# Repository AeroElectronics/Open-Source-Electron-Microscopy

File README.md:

# Open Source Electron Microscopy

This is not the first or last attempt at making open source electron microscopy a reality. Many others have attempted this large and difficult task before with varying specialties and contributions. I have learned a great deal from other's work in this area and it is my hope that I can make a contribution too. It is through the collective effort and ability of the open source community that progress on such large and difficult tasks may be realized.

My work so far has focused on the control electronics which can be used to drive electron microscopes. This is an essential first step that can (mostly) preceed the design of the electron optics. I'm hoping that by lowering the barrier to entry, others can work on this exciting task.

**Note to readers! This repo is quite new, many of the currently uploaded works are my most recent iterations (old designs have not been uploaded) and have not yet been tested. Please check the **

I've worked on a few areas, see the links below:

[Backplane](./Backplane/README.md)

[Coil drivers](./DeflectionCoilDrivers/README.md)

[Resistor/Inductor Substitution board](./SubstitutionBoard/README.md)

[Raster generator](./RasterGenerator/README.md)

Remember, this project is still under development. Use at your own risk. This work is licenced under CERN OHL V2 S. Please see license file.

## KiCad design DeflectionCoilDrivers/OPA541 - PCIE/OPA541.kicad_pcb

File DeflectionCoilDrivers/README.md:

# Deflecion Coil Drivers
Deflection coil drivers are the electronics that push current into the magnetic lenses that raster the electron beam around the sample. A good deflection coil driver is high bandwidth, fast slewing, low noise, low distortion, low drift, and can operate over a large dynamic range. These constraints make practical design considerably more involved than I anticipated.

First, a few notes on deflection coil drivers generally. Since the magnetic field produced by a deflection coil is proportional to the current through it. This means that a deflection coil driver is essentially a 'transconductance amplifier' which converts a voltage signal input (from a DAC or something) that requests current, to a realized current on the coil.

Existing electron microscopes have used a variety of design approaches. I have designed several deflection coil drivers, shown below.

## Single ended coil driver
Single ended coil drivers are where you control the voltage on one side of your load, and ground the other side. This is simpler than a bridge topology and easier to work with generally, but it makes the sacrifice of giving up halving the maximum voltage difference you can apply to your load and limiting your slew rate as compared to two amplifiers. These designs are comparitively easy to work with and one require one power OpAmp and some supporting electronics. If you are ok with slow speeds, single ended is likely fine.

The picture below is my latest iteration of a somewhat but not entirely tested version. Will report back after testing this one.

## Bridge topology howland current pump
The bridge topology howland current pump is essentially two power OpAmps which act to source and sink current to and from the load. The load is positioned between the outputs of the two power OpAmps. With this topology the slew rate and maximum achivable voltage doubles as compared to a single ended design where one end of the load is grounded. I attempted this design using OPA548 amplifiers but was displeased with the speed. I have redesigned this board to accept other opamps and will revisit this in the future.

The picture below I have partially tested with some modifications. After some pain, I now think the OPA548 may be unsuitable for the task.

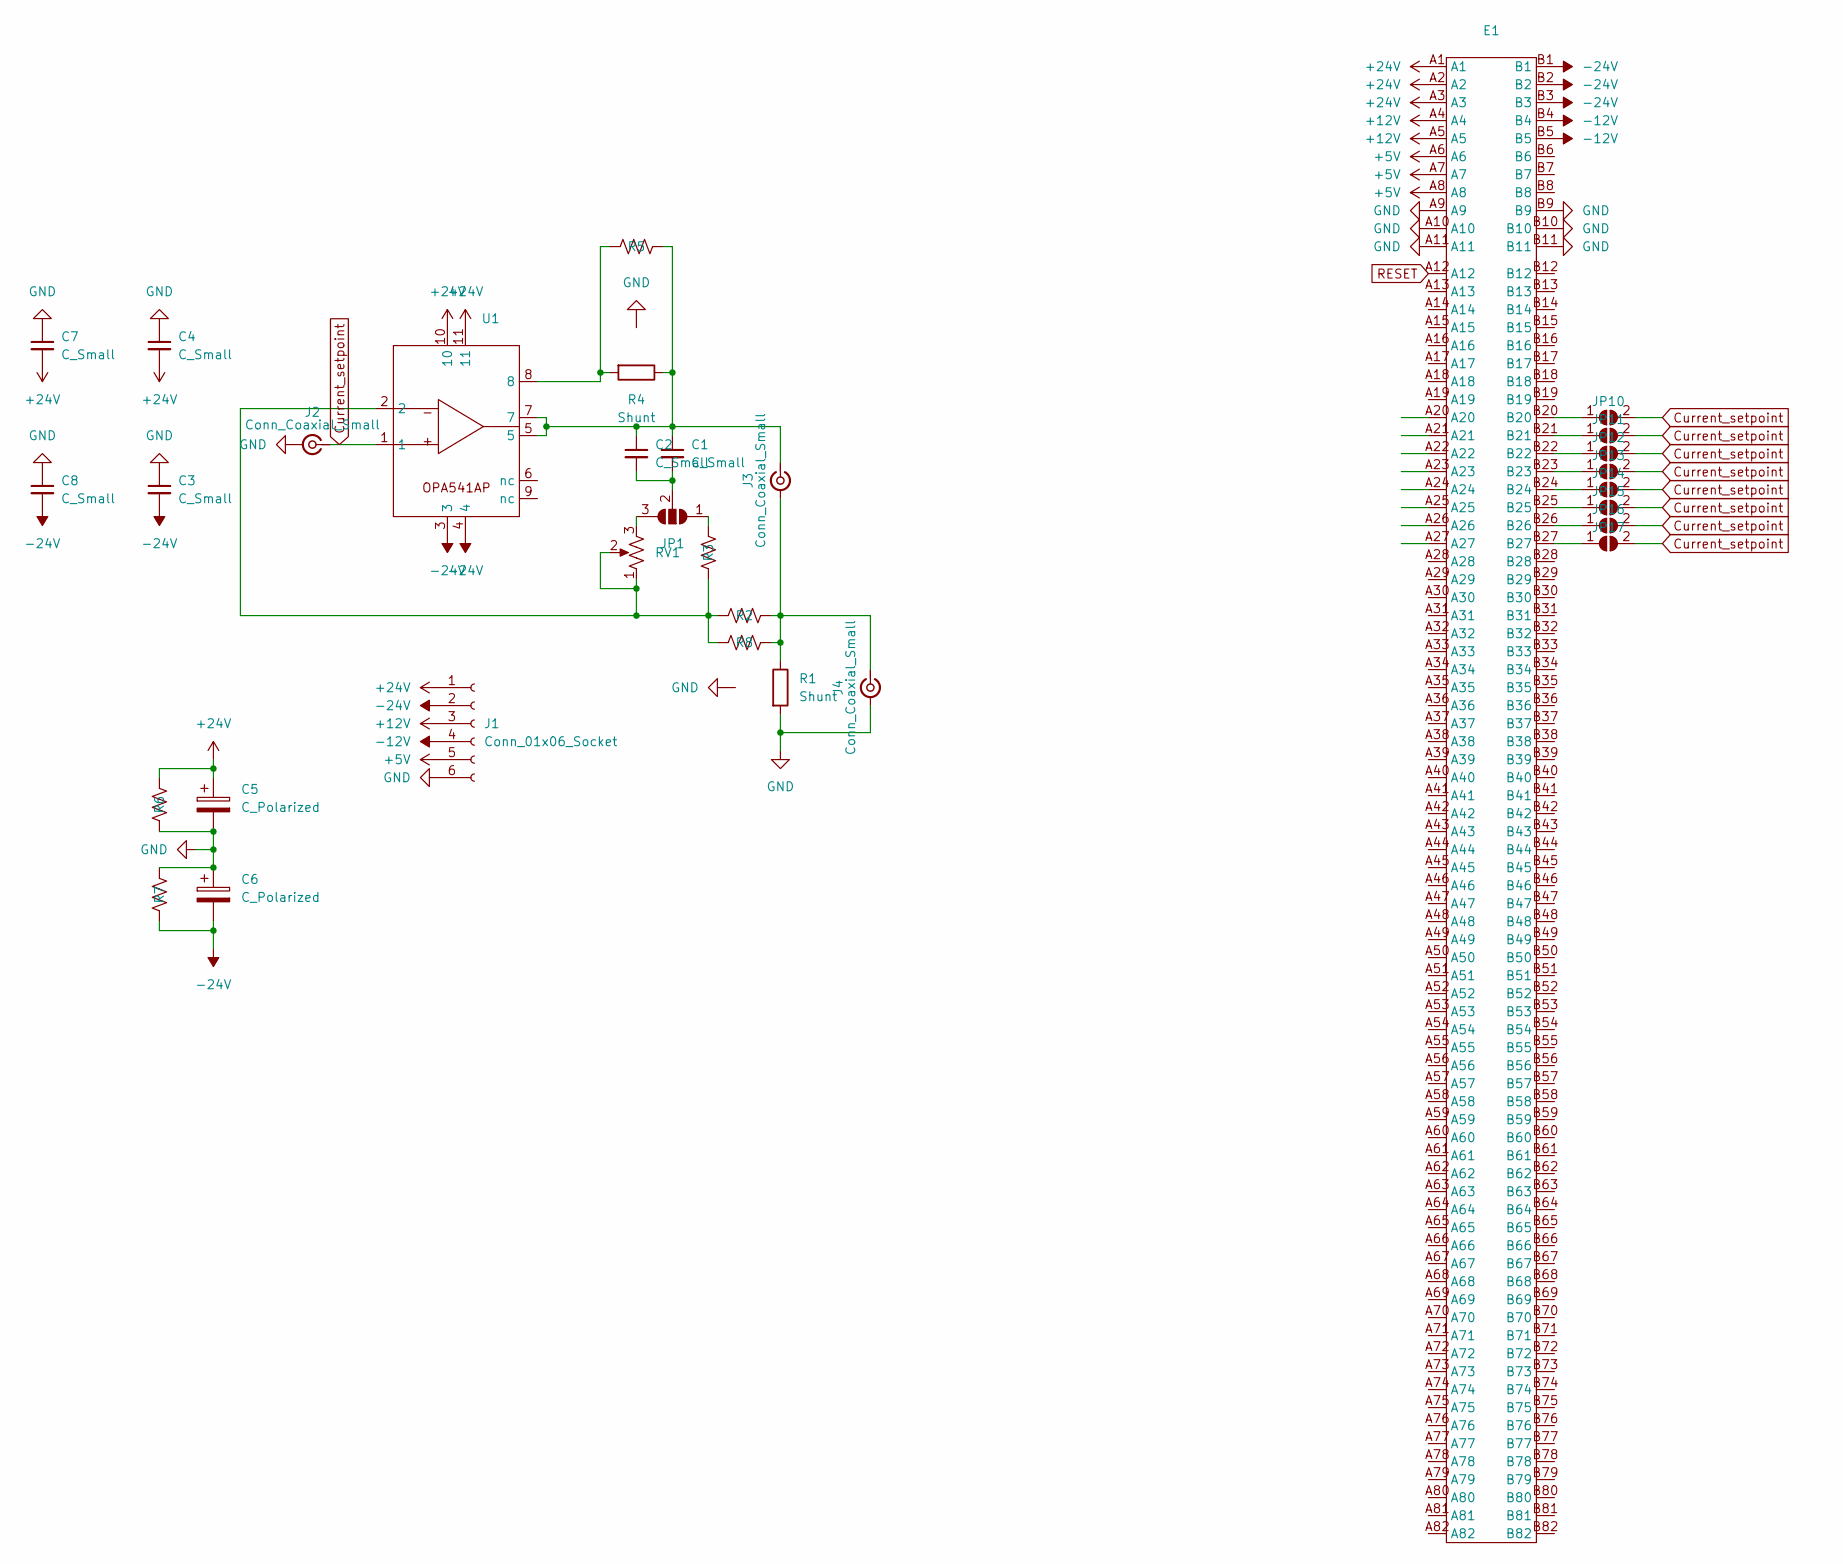
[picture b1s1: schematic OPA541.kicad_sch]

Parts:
C1, C3, C4, C7, C8: C_Small; C_0603_1608Metric_Pad1.08x0.95mm_HandSolder
C2: C_Small; C_Disc_D6.0mm_W2.5mm_P5.00mm
C5, C6: C_Polarized; CP_Radial_D10.0mm_P5.00mm
E1: BUS_PCIexpress_x16
J1: Conn_01x06_Socket; PhoenixContact_MC_1,5_6-GF-3.81_1x06_P3.81mm_Horizontal_Thr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
J2, J3, J4: Conn_Coaxial_Small; BNC_Amphenol_B6252HB-NPP3G-50_Horizontal
JP1: SolderJumper_3_Open; SolderJumper-3_P1.3mm_Open_RoundedPad1.0x1.5mm
JP10, JP11, JP12, JP13, JP14, JP15, JP16, JP17: SolderJumper_2_Open; SolderJumper-2_P1.3mm_Open_RoundedPad1.0x1.5mm
R1, R4: Shunt; TO-263-2_TabPin1
R2: 1k; C_0603_1608Metric_Pad1.08x0.95mm_HandSolder
R3: 20k; C_0603_1608Metric_Pad1.08x0.95mm_HandSolder
R5: 0.3; R_Axial_DIN0204_L3.6mm_D1.6mm_P7.62mm_Horizontal
R6, R7: 100k; R_0603_1608Metric_Pad0.98x0.95mm_HandSolder
R8: 1k; C_Disc_D6.0mm_W2.5mm_P5.00mm
RV1: R_Potentiometer_US; Potentiometer_Bourns_3269P_Horizontal
U1: TO-220-11_P3.4x5.08mm_StaggerOdd_Lead4.85mm_Vertical

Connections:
+5V: E1.A6, E1.A7, E1.A8, J1.5
+12V: E1.A4, E1.A5, J1.3
+24V: C4.2, C5.1, C7.2, E1.A1, E1.A2, E1.A3, J1.1, R6.2, U1.10, U1.11
-12V: E1.B4, E1.B5, J1.4
-24V: C3.2, C6.2, C8.2, E1.B1, E1.B2, E1.B3, J1.2, R7.1, U1.3, U1.4
Current_setpoint: J2.1 (In), JP10.2 (B), JP11.2 (B), JP12.2 (B), JP13.2 (B), JP14.2 (B), JP15.2 (B), JP16.2 (B), JP17.2 (B), U1.1
GND: C3.1, C4.1, C5.2, C6.1, C7.1, C8.1, E1.A9, E1.A10, E1.A11, E1.B9, E1.B10, E1.B11, J1.6, J2.2 (Ext), J4.2 (Ext), R1.2, R1.3, R4.3, R6.1, R7.2
unnamed: J3.2 (Ext), J4.1 (In), R1.1, R2.2, R8.2
unnamed: C1.1, C2.1, J3.1 (In), R4.1, R5.2, U1.5, U1.7
unnamed: JP1.1 (A), R3.1
unnamed: JP1.3 (B), RV1.3
unnamed: C1.2, C2.2, JP1.2 (C)
unnamed: E1.B20, JP10.1 (A)
unnamed: E1.B21, JP11.1 (A)
unnamed: E1.B22, JP12.1 (A)
unnamed: E1.B23, JP13.1 (A)
unnamed: E1.B24, JP14.1 (A)
unnamed: E1.B25, JP15.1 (A)
unnamed: E1.B26, JP16.1 (A)
unnamed: E1.B27, JP17.1 (A)
unnamed: R2.1, R3.2, R8.1, RV1.1, RV1.2, U1.2
unnamed: R4.2, R5.1, U1.8
RESET: E1.A12

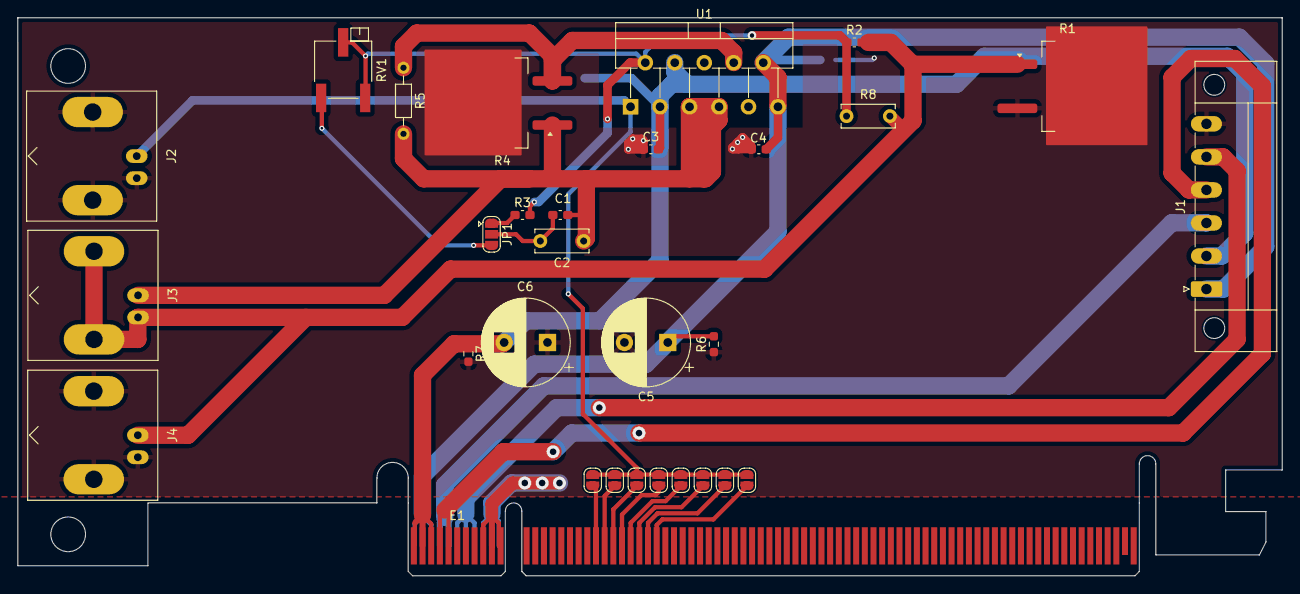
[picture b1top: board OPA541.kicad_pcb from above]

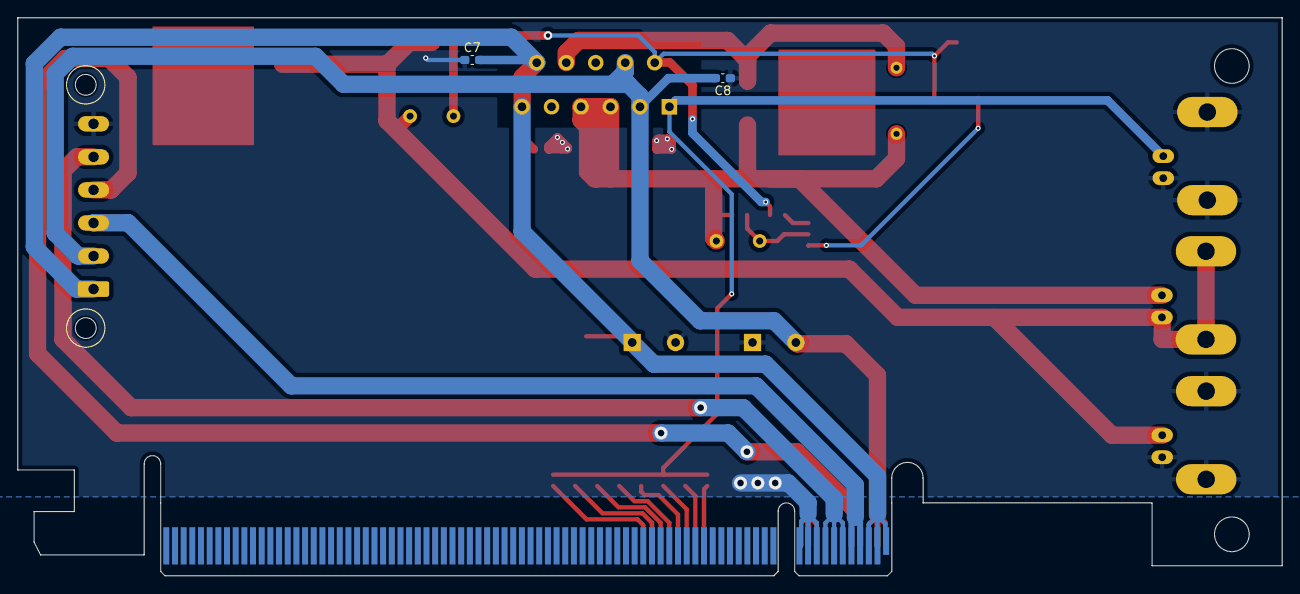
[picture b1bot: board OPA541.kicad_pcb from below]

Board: 2 copper layers, 145.8 x 64.3 mm, 32 parts (2 on the bottom side), 22 nets.

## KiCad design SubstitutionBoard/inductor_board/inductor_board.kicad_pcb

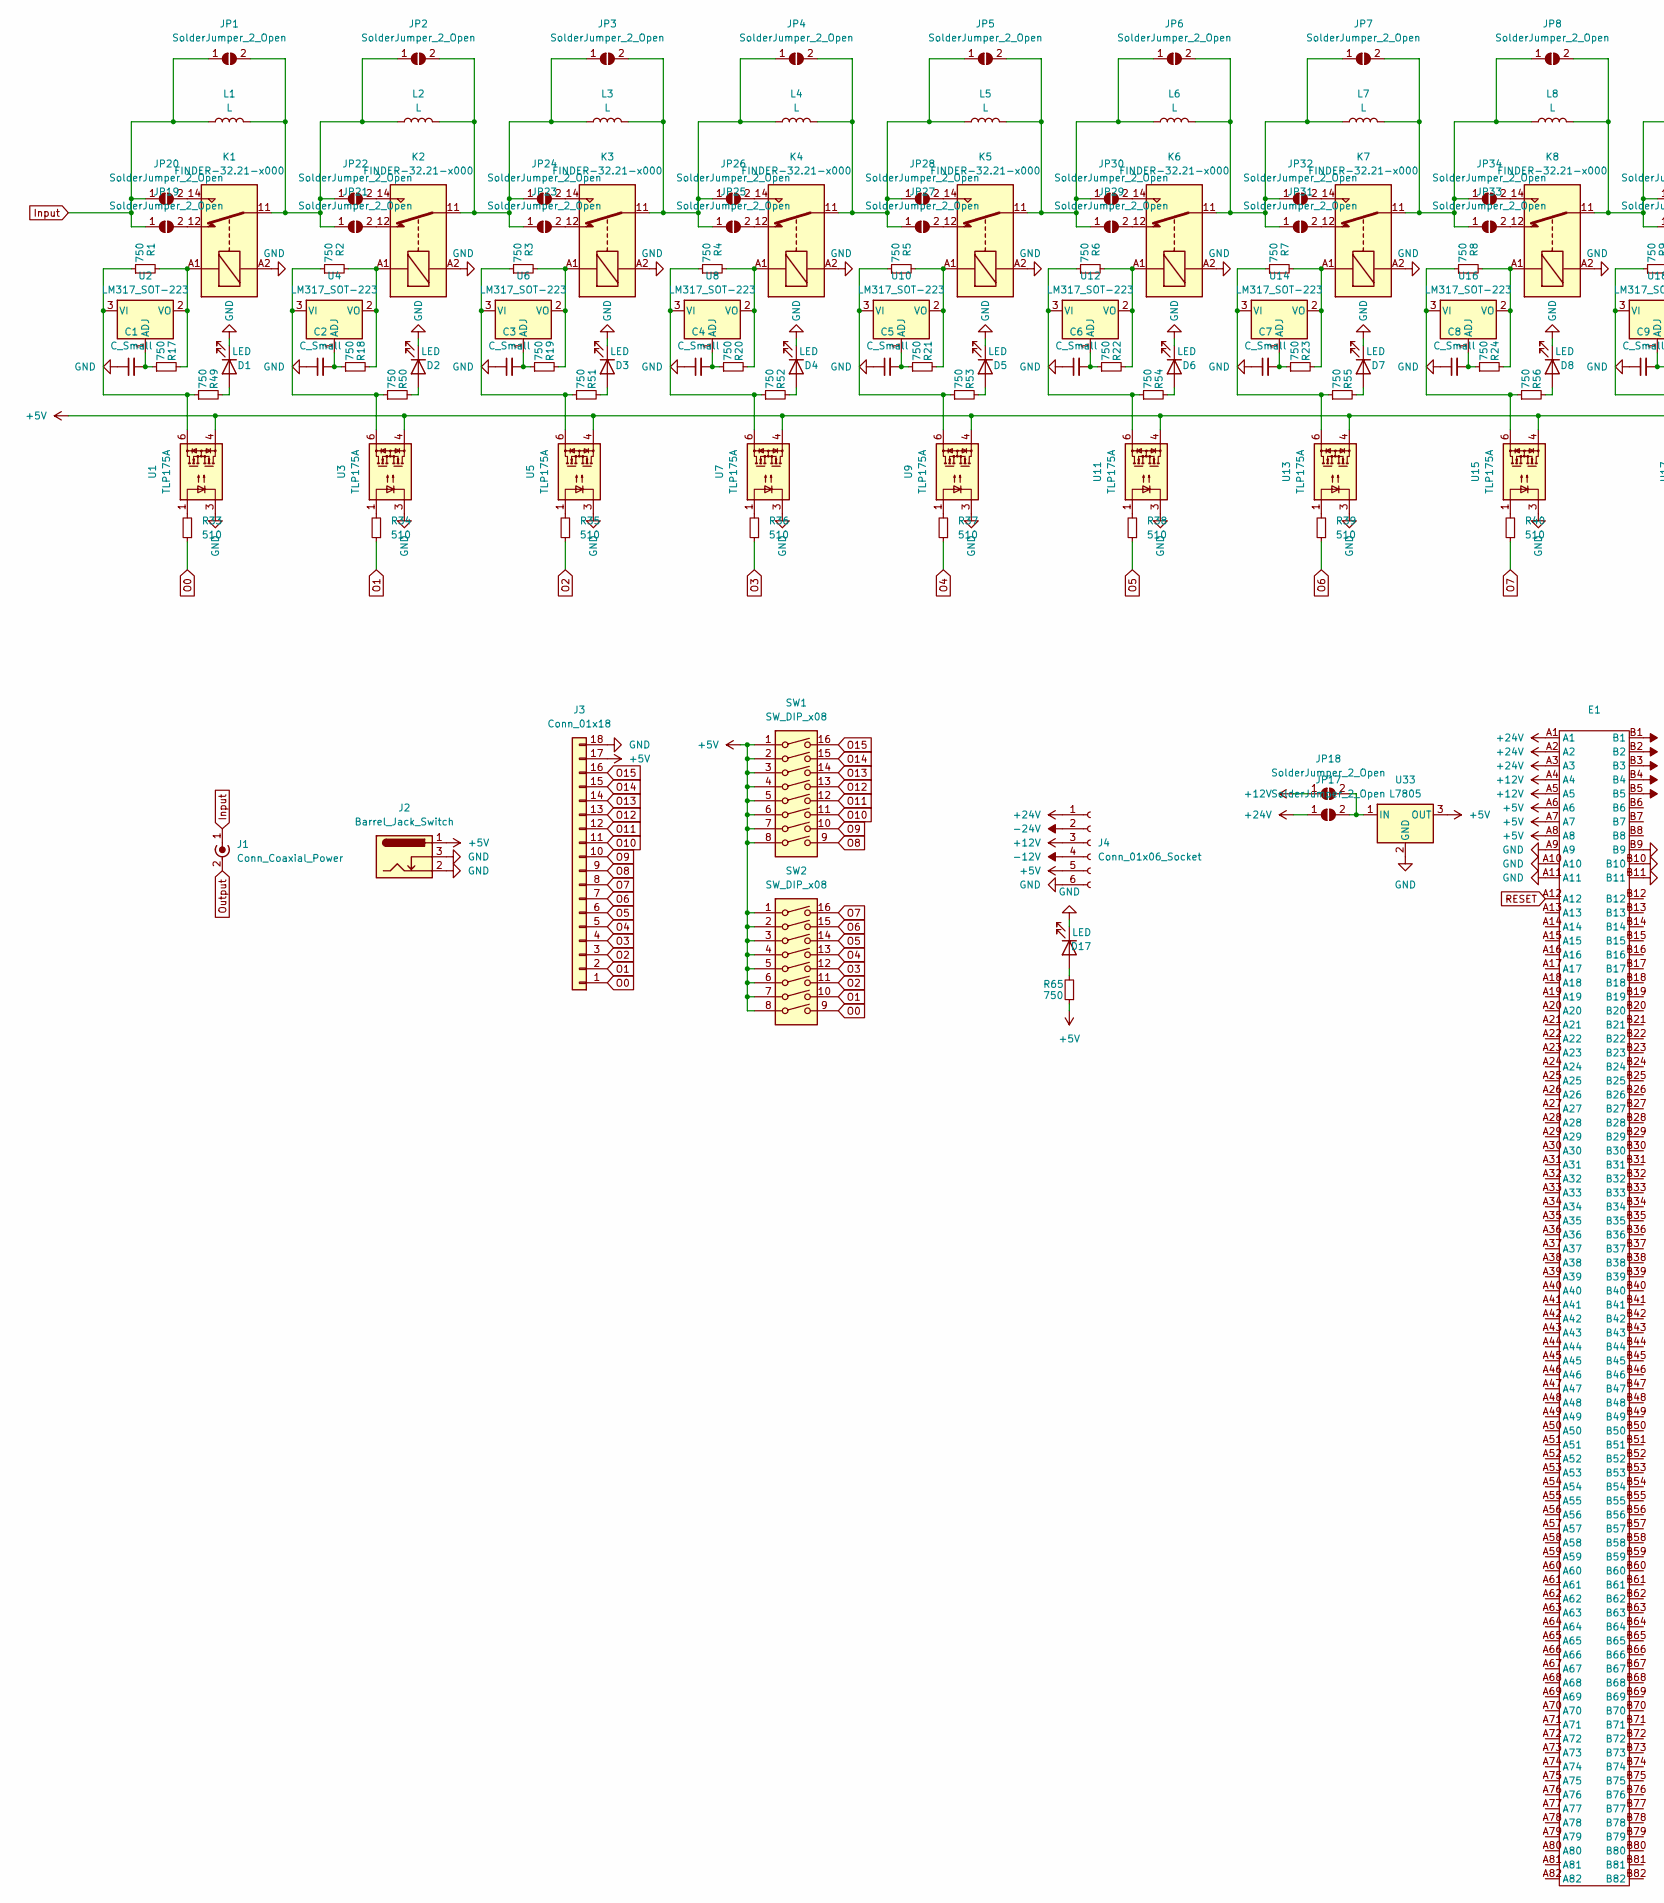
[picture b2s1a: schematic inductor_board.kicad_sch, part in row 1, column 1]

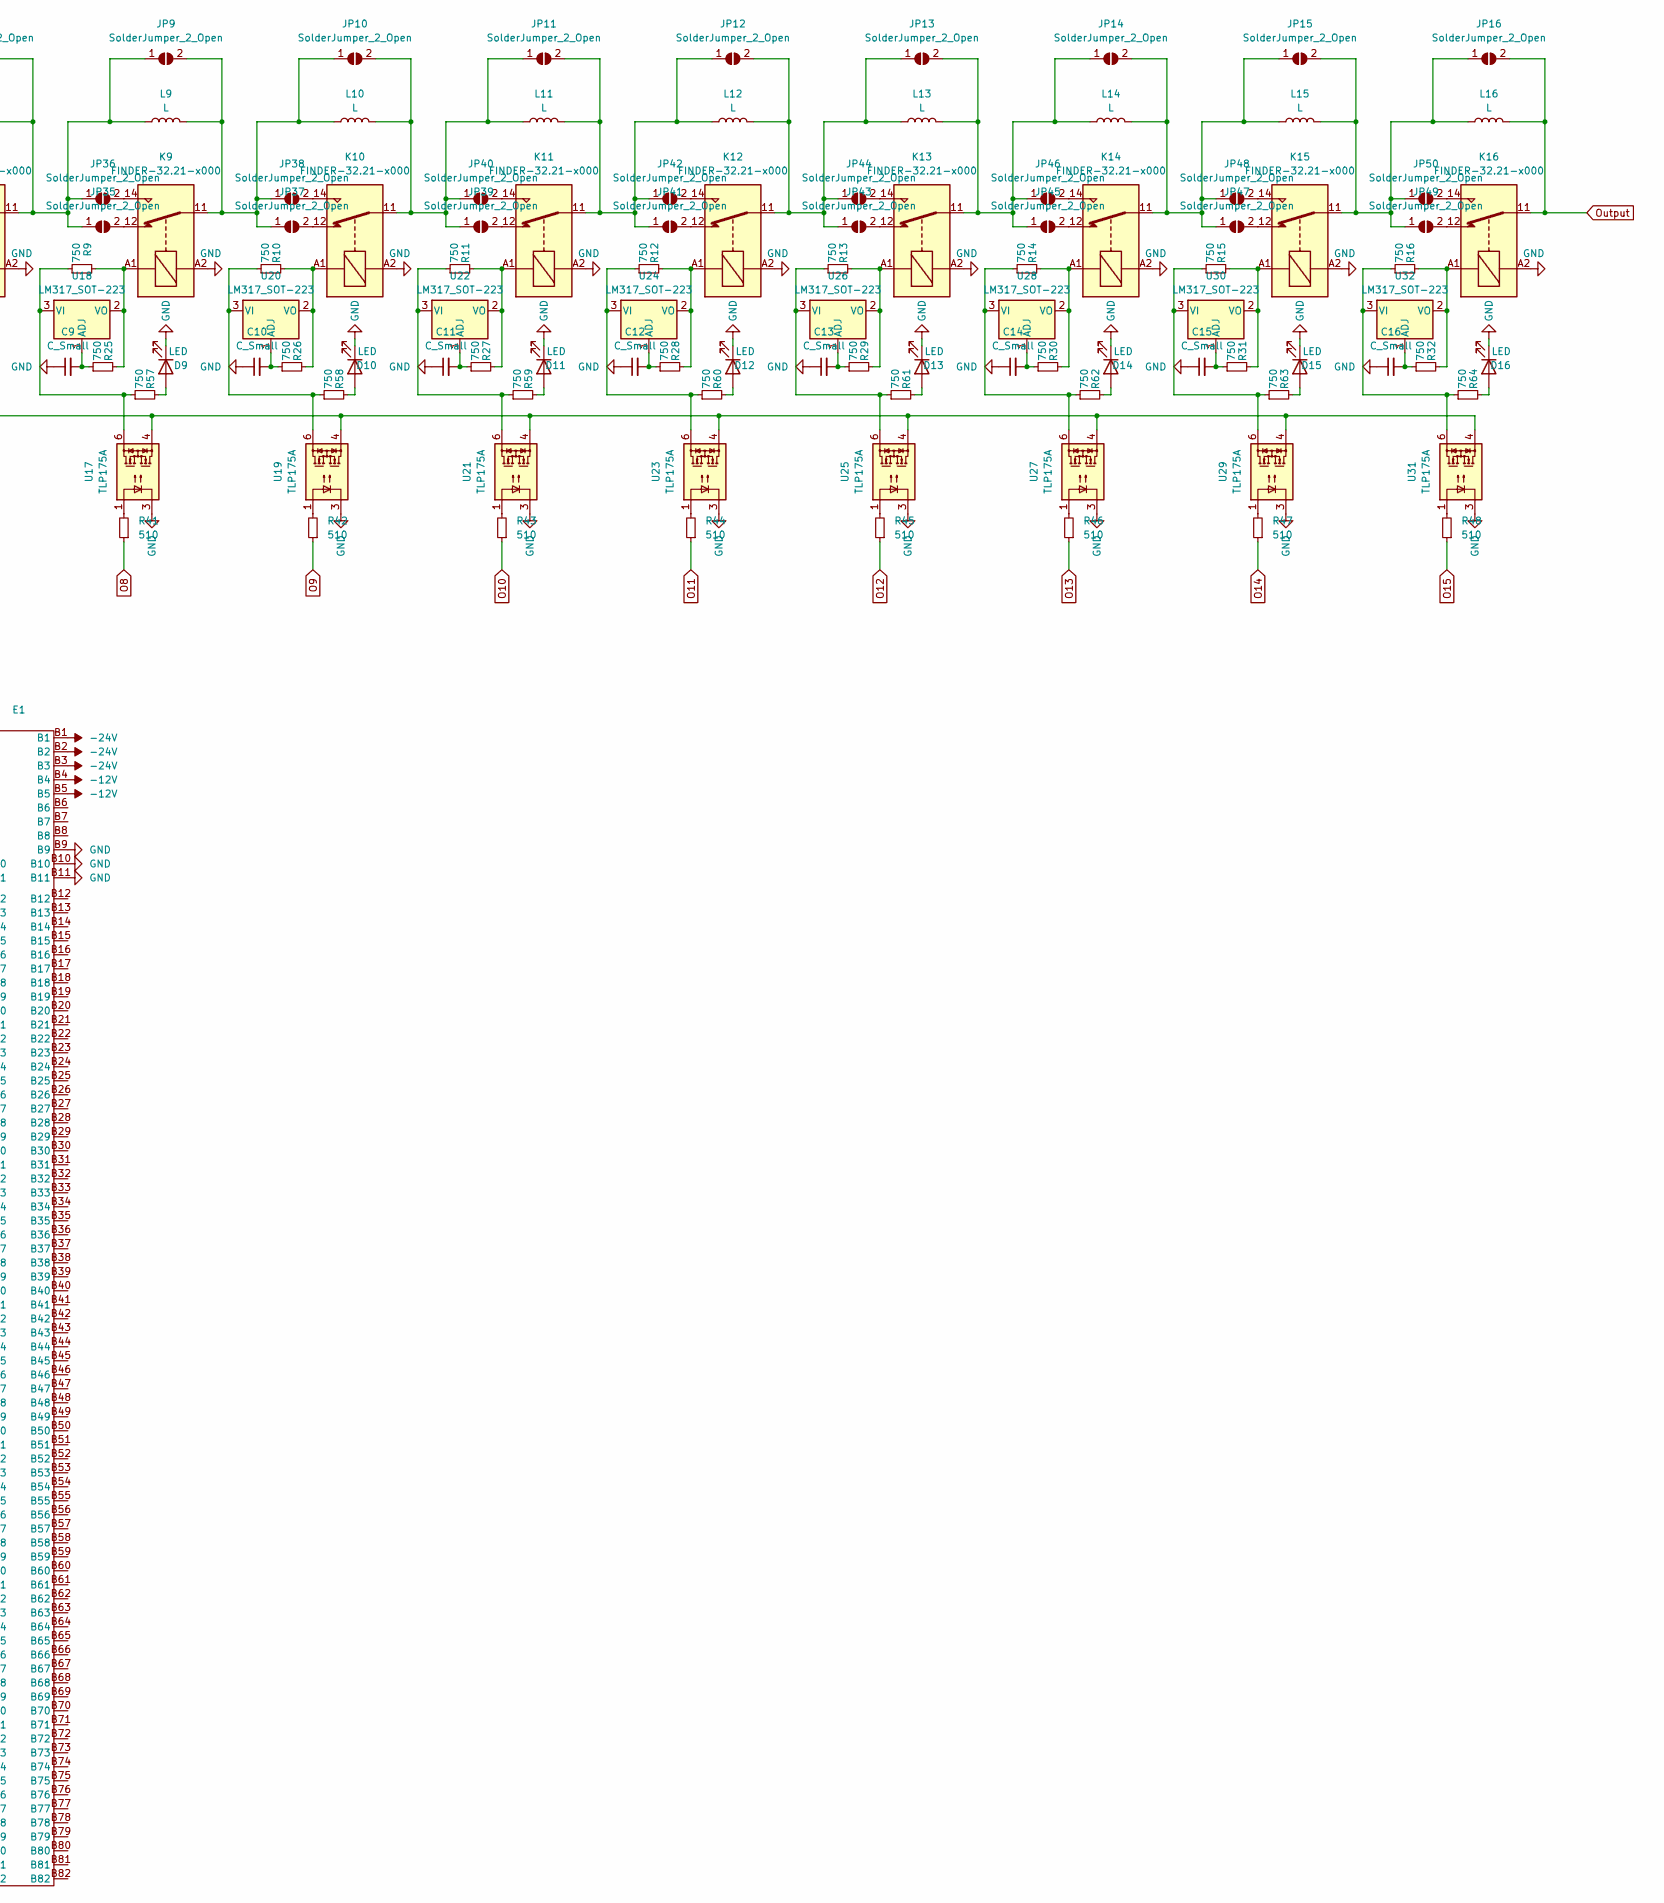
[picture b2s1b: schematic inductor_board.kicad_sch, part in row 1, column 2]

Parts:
C1, C2, C3, C4, C5, C6, C7, C8, C9, C10, C11, C12, C13, C14, C15, C16: C_Small; C_0805_2012Metric_Pad1.18x1.45mm_HandSolder
D1, D2, D3, D4, D5, D6, D7, D8, D9, D10, D11, D12, D13, D14, D15, D16, D17: LED; LED_0603_1608Metric_Pad1.05x0.95mm_HandSolder
E1: BUS_PCIexpress_x16
J1: Conn_Coaxial_Power; BNC_Amphenol_B6252HB-NPP3G-50_Horizontal
J2: Barrel_Jack_Switch; BarrelJack_GCT_DCJ200-10-A_Horizontal
J3: Conn_01x18; PinHeader_1x18_P2.54mm_Vertical
J4: Conn_01x06_Socket; PhoenixContact_MC_1,5_6-GF-3.81_1x06_P3.81mm_Horizontal_Thr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
JP1, JP2, JP3, JP4, JP5, JP6, JP7, JP8, JP9, JP10, JP11, JP12, JP13, JP14, JP15, JP16, JP17, JP18, JP19, JP20, JP21, JP22, JP23, JP24, JP25, JP26, JP27, JP28, JP29, JP30, JP31, JP32, JP33, JP34, JP35, JP36, JP37, JP38, JP39, JP40, JP41, JP42, JP43, JP44, JP45, JP46, JP47, JP48, JP49, JP50: SolderJumper_2_Open; SolderJumper-2_P1.3mm_Open_RoundedPad1.0x1.5mm
K1, K2, K3, K4, K5, K6, K7, K8, K9, K10, K11, K12, K13, K14, K15, K16: FINDER-32.21-x000; Relay_SPDT_Finder_32.21-x000
L1, L2, L3, L4, L5, L6, L7, L8, L9, L10, L11, L12, L13, L14, L15, L16: L; coilcraftRFS
R1, R2, R3, R4, R5, R6, R7, R8, R9, R10, R11, R12, R13, R14, R15, R16: 750; R_0805_2012Metric_Pad1.20x1.40mm_HandSolder
R17, R18, R19, R20, R21, R22, R23, R24, R25, R26, R27, R28, R29, R30, R31, R32, R49, R50, R51, R52, R53, R54, R55, R56, R57, R58, R59, R60, R61, R62, R63, R64, R65: 750; R_0603_1608Metric_Pad0.98x0.95mm_HandSolder
R33, R34, R35, R36, R37, R38, R39, R40, R41, R42, R43, R44, R45, R46, R47, R48: 510; R_0603_1608Metric_Pad0.98x0.95mm_HandSolder
SW1, SW2: SW_DIP_x08; SW_DIP_SPSTx08_Slide_9.78x22.5mm_W7.62mm_P2.54mm
U1, U3, U5, U7, U9, U11, U13, U15, U17, U19, U21, U23, U25, U27, U29, U31: TLP175A; MFSOP6-4_4.4x3.6mm_P1.27mm
U2, U4, U6, U8, U10, U12, U14, U16, U18, U20, U22, U24, U26, U28, U30, U32: LM317_SOT-223; SOT-223-3_TabPin2
U33: L7805; TO-252-3_TabPin2

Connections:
+5V: E1.A6, E1.A7, E1.A8, J2.1, J3.17, J4.5, R65.1, SW1.1, SW1.2, SW1.3, SW1.4, SW1.5, SW1.6, SW1.7, SW1.8, SW2.1, SW2.2, SW2.3, SW2.4, SW2.5, SW2.6, SW2.7, SW2.8, U1.4, U3.4, U5.4, U7.4, U9.4, U11.4, U13.4, U15.4, U17.4, U19.4, U21.4, U23.4, U25.4, U27.4, U29.4, U31.4, U33.3 (OUT)
+12V: E1.A4, E1.A5, J4.3, JP18.1 (A)
+24V: E1.A1, E1.A2, E1.A3, J4.1, JP17.1 (A)
-12V: E1.B4, E1.B5, J4.4
-24V: E1.B1, E1.B2, E1.B3, J4.2
GND: C1.1, C2.1, C3.1, C4.1, C5.1, C6.1, C7.1, C8.1, C9.1, C10.1, C11.1, C12.1, C13.1, C14.1, C15.1, C16.1, D1.1 (K), D2.1 (K), D3.1 (K), D4.1 (K), D5.1 (K), D6.1 (K), D7.1 (K), D8.1 (K), D9.1 (K), D10.1 (K), D11.1 (K), D12.1 (K), D13.1 (K), D14.1 (K), D15.1 (K), D16.1 (K), D17.1 (K), E1.A9, E1.A10, E1.A11, E1.B9, E1.B10, E1.B11, J2.2, J2.3, J3.18, J4.6, K1.A2, K2.A2, K3.A2, K4.A2, K5.A2, K6.A2, K7.A2, K8.A2, K9.A2, K10.A2, K11.A2, K12.A2, K13.A2, K14.A2, K15.A2, K16.A2, U1.3, U3.3, U5.3, U7.3, U9.3, U11.3, U13.3, U15.3, U17.3, U19.3, U21.3, U23.3, U25.3, U27.3, U29.3, U31.3, U33.2 (GND)
Input: J1.1 (In), JP1.1 (A), JP19.1 (A), JP20.1 (A), L1.1
unnamed: D1.2 (A), R49.2
unnamed: D2.2 (A), R50.2
unnamed: D3.2 (A), R51.2
unnamed: D4.2 (A), R52.2
unnamed: D5.2 (A), R53.2
unnamed: D6.2 (A), R54.2
unnamed: D7.2 (A), R55.2
unnamed: D8.2 (A), R56.2
unnamed: D9.2 (A), R57.2
unnamed: D10.2 (A), R58.2
unnamed: D11.2 (A), R59.2
unnamed: D12.2 (A), R60.2
unnamed: D13.2 (A), R61.2
unnamed: D14.2 (A), R62.2
unnamed: D15.2 (A), R63.2
unnamed: D16.2 (A), R64.2
unnamed: D17.2 (A), R65.2
unnamed: JP1.2 (B), JP2.1 (A), JP21.1 (A), JP22.1 (A), K1.11, L1.2, L2.1
unnamed: JP2.2 (B), JP3.1 (A), JP23.1 (A), JP24.1 (A), K2.11, L2.2, L3.1
unnamed: JP9.2 (B), JP10.1 (A), JP37.1 (A), JP38.1 (A), K9.11, L9.2, L10.1
unnamed: JP10.2 (B), JP11.1 (A), JP39.1 (A), JP40.1 (A), K10.11, L10.2, L11.1
unnamed: JP11.2 (B), JP12.1 (A), JP41.1 (A), JP42.1 (A), K11.11, L11.2, L12.1
unnamed: JP12.2 (B), JP13.1 (A), JP43.1 (A), JP44.1 (A), K12.11, L12.2, L13.1
unnamed: JP13.2 (B), JP14.1 (A), JP45.1 (A), JP46.1 (A), K13.11, L13.2, L14.1
unnamed: JP14.2 (B), JP15.1 (A), JP47.1 (A), JP48.1 (A), K14.11, L14.2, L15.1
unnamed: JP15.2 (B), JP16.1 (A), JP49.1 (A), JP50.1 (A), K15.11, L15.2, L16.1
unnamed: JP17.2 (B), JP18.2 (B), U33.1 (IN)
unnamed: JP19.2 (B), K1.12
unnamed: JP20.2 (B), K1.14
unnamed: JP21.2 (B), K2.12
unnamed: JP22.2 (B), K2.14
unnamed: JP23.2 (B), K3.12
unnamed: JP24.2 (B), K3.14
unnamed: JP3.2 (B), JP4.1 (A), JP25.1 (A), JP26.1 (A), K3.11, L3.2, L4.1
unnamed: JP25.2 (B), K4.12
unnamed: JP26.2 (B), K4.14
unnamed: JP4.2 (B), JP5.1 (A), JP27.1 (A), JP28.1 (A), K4.11, L4.2, L5.1
unnamed: JP27.2 (B), K5.12
unnamed: JP28.2 (B), K5.14
unnamed: JP5.2 (B), JP6.1 (A), JP29.1 (A), JP30.1 (A), K5.11, L5.2, L6.1
unnamed: JP29.2 (B), K6.12
unnamed: JP30.2 (B), K6.14
unnamed: JP6.2 (B), JP7.1 (A), JP31.1 (A), JP32.1 (A), K6.11, L6.2, L7.1
unnamed: JP31.2 (B), K7.12
unnamed: JP32.2 (B), K7.14
unnamed: JP7.2 (B), JP8.1 (A), JP33.1 (A), JP34.1 (A), K7.11, L7.2, L8.1
unnamed: JP33.2 (B), K8.12
unnamed: JP34.2 (B), K8.14
unnamed: JP8.2 (B), JP9.1 (A), JP35.1 (A), JP36.1 (A), K8.11, L8.2, L9.1
unnamed: JP35.2 (B), K9.12
unnamed: JP36.2 (B), K9.14
unnamed: JP37.2 (B), K10.12
unnamed: JP38.2 (B), K10.14
unnamed: JP39.2 (B), K11.12
unnamed: JP40.2 (B), K11.14
unnamed: JP41.2 (B), K12.12
unnamed: JP42.2 (B), K12.14
unnamed: JP43.2 (B), K13.12
unnamed: JP44.2 (B), K13.14
unnamed: JP45.2 (B), K14.12
unnamed: JP46.2 (B), K14.14
unnamed: JP47.2 (B), K15.12
unnamed: JP48.2 (B), K15.14
unnamed: JP49.2 (B), K16.12
unnamed: JP50.2 (B), K16.14
unnamed: R33.2, U1.1
unnamed: R34.2, U3.1
unnamed: R35.2, U5.1
unnamed: R36.2, U7.1
unnamed: R37.2, U9.1
unnamed: R38.2, U11.1
unnamed: R39.2, U13.1
unnamed: R40.2, U15.1
unnamed: R41.2, U17.1
unnamed: R42.2, U19.1
unnamed: R43.2, U21.1
unnamed: R44.2, U23.1
unnamed: R45.2, U25.1
unnamed: R46.2, U27.1
unnamed: R47.2, U29.1
unnamed: R48.2, U31.1
unnamed: C1.2, R17.1, U2.1 (ADJ)
unnamed: R1.1, R49.1, U1.6, U2.3 (VI)
unnamed: K1.A1, R1.2, R17.2, U2.2 (VO)
unnamed: C2.2, R18.1, U4.1 (ADJ)
unnamed: R2.1, R50.1, U3.6, U4.3 (VI)
unnamed: K2.A1, R2.2, R18.2, U4.2 (VO)
unnamed: C3.2, R19.1, U6.1 (ADJ)
unnamed: R3.1, R51.1, U5.6, U6.3 (VI)
unnamed: K3.A1, R3.2, R19.2, U6.2 (VO)
unnamed: C4.2, R20.1, U8.1 (ADJ)
unnamed: R4.1, R52.1, U7.6, U8.3 (VI)
unnamed: K4.A1, R4.2, R20.2, U8.2 (VO)
unnamed: C5.2, R21.1, U10.1 (ADJ)
unnamed: R5.1, R53.1, U9.6, U10.3 (VI)
unnamed: K5.A1, R5.2, R21.2, U10.2 (VO)
unnamed: C6.2, R22.1, U12.1 (ADJ)
unnamed: R6.1, R54.1, U11.6, U12.3 (VI)
unnamed: K6.A1, R6.2, R22.2, U12.2 (VO)
unnamed: C7.2, R23.1, U14.1 (ADJ)
unnamed: R7.1, R55.1, U13.6, U14.3 (VI)
unnamed: K7.A1, R7.2, R23.2, U14.2 (VO)
unnamed: C8.2, R24.1, U16.1 (ADJ)
unnamed: R8.1, R56.1, U15.6, U16.3 (VI)
unnamed: K8.A1, R8.2, R24.2, U16.2 (VO)
unnamed: C9.2, R25.1, U18.1 (ADJ)
unnamed: R9.1, R57.1, U17.6, U18.3 (VI)
unnamed: K9.A1, R9.2, R25.2, U18.2 (VO)
unnamed: C10.2, R26.1, U20.1 (ADJ)
unnamed: R10.1, R58.1, U19.6, U20.3 (VI)
unnamed: K10.A1, R10.2, R26.2, U20.2 (VO)
unnamed: C11.2, R27.1, U22.1 (ADJ)
unnamed: R11.1, R59.1, U21.6, U22.3 (VI)
unnamed: K11.A1, R11.2, R27.2, U22.2 (VO)
unnamed: C12.2, R28.1, U24.1 (ADJ)
unnamed: R12.1, R60.1, U23.6, U24.3 (VI)
unnamed: K12.A1, R12.2, R28.2, U24.2 (VO)
unnamed: C13.2, R29.1, U26.1 (ADJ)
unnamed: R13.1, R61.1, U25.6, U26.3 (VI)
unnamed: K13.A1, R13.2, R29.2, U26.2 (VO)
unnamed: C14.2, R30.1, U28.1 (ADJ)
unnamed: R14.1, R62.1, U27.6, U28.3 (VI)
unnamed: K14.A1, R14.2, R30.2, U28.2 (VO)
unnamed: C15.2, R31.1, U30.1 (ADJ)
unnamed: R15.1, R63.1, U29.6, U30.3 (VI)
unnamed: K15.A1, R15.2, R31.2, U30.2 (VO)
unnamed: C16.2, R32.1, U32.1 (ADJ)
unnamed: R16.1, R64.1, U31.6, U32.3 (VI)
unnamed: K16.A1, R16.2, R32.2, U32.2 (VO)
O0: J3.1, R33.1, SW2.9
O1: J3.2, R34.1, SW2.10
O2: J3.3, R35.1, SW2.11
O3: J3.4, R36.1, SW2.12
O4: J3.5, R37.1, SW2.13
O5: J3.6, R38.1, SW2.14
O6: J3.7, R39.1, SW2.15
O7: J3.8, R40.1, SW2.16
O8: J3.9, R41.1, SW1.9
O9: J3.10, R42.1, SW1.10
O10: J3.11, R43.1, SW1.11
O11: J3.12, R44.1, SW1.12
O12: J3.13, R45.1, SW1.13
O13: J3.14, R46.1, SW1.14
O14: J3.15, R47.1, SW1.15
O15: J3.16, R48.1, SW1.16
Output: J1.2 (Ext), JP16.2 (B), K16.11, L16.2
RESET: E1.A12

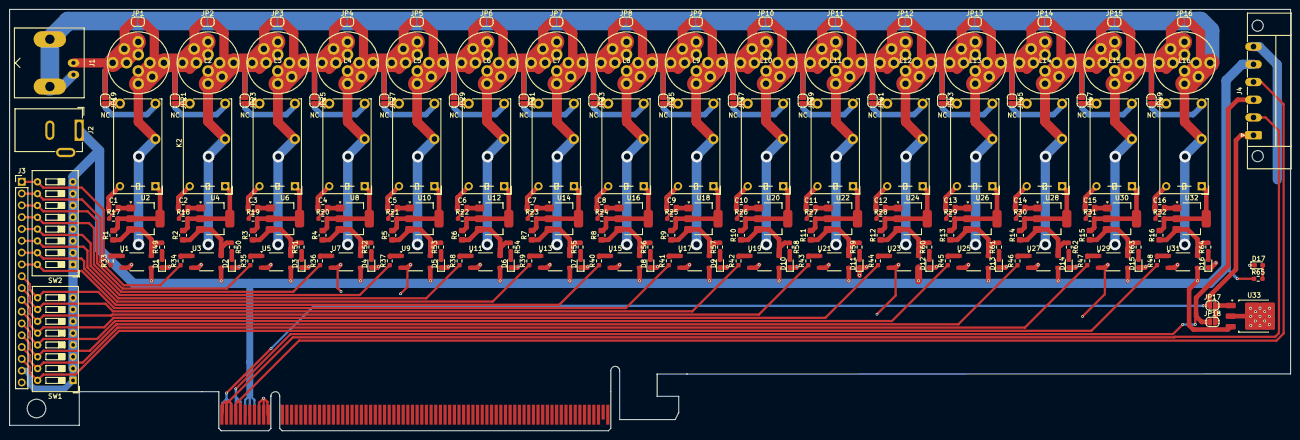
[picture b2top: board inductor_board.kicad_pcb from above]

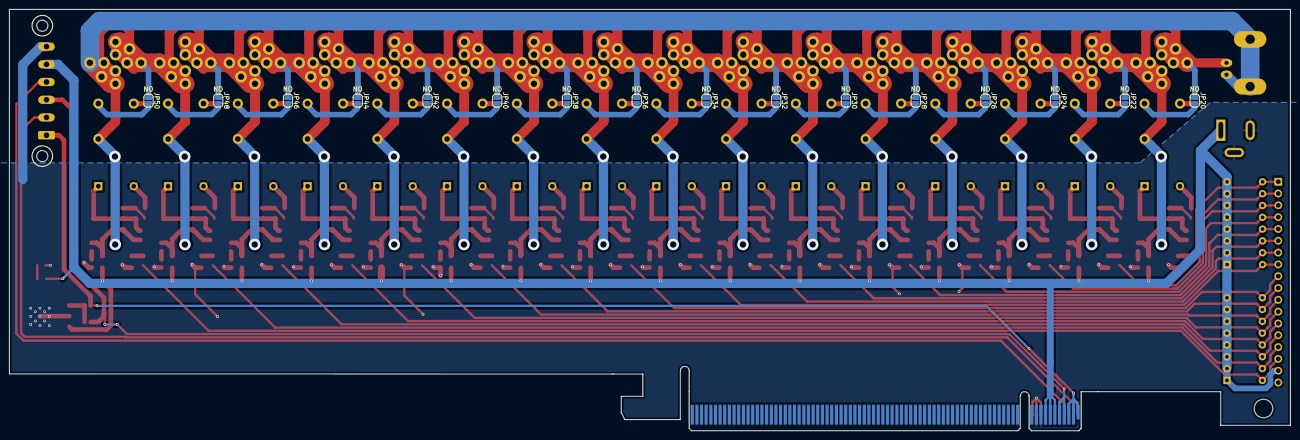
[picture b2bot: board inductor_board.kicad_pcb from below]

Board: 2 copper layers, 275.5 x 90.6 mm, 220 parts (16 on the bottom side), 153 nets.

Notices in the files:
parts and their libraries:
Copyright 2021 Accelerated Designs. All rights reserved.
